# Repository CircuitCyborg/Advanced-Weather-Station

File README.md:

# Advanced-Weather-Station

Local Weather Station that incorporates weather from the user location and displays everything on a local desk base station.

Possible Future Features -

Incorporating forecast from a weather service onto the Base Station.
Communication between modules through the LAN
Limited Smart Home Automations through Base Station

To view the Weather Station in 3D Open this link: https://cad.onshape.com/documents/2aa1986e22143bf0c5bf430b/w/d39aab6bbb374c6101d395f4/e/43a2d6a15468c7d35dd3c23b?renderMode=0&uiState=6ae6a9e5bb2c688de4aefb5d

The purpose of designing this project was to have the most accurate weather information for my exact location. Weather apps are cool, but they are just a reading of where the weather module is for that company. My weather station gives a reading of what my exact location's weather is instead so I will have the most accurate weather data for my location.

For the few who want to build this themselves, there will be a bit of hand wiring that will have to happen. For this wiring, you will need 10 conductors for the direction sensor, 3 conductors for the temp/humidity sensor, 3 for the wind speed sensor, and 3 for the precipitation module. If you purchase enough, you should be able to use the extra ethercon cable for those conductors. When wiring, take your time, be patient with yourself, and have fun!

Wiring Diagram:

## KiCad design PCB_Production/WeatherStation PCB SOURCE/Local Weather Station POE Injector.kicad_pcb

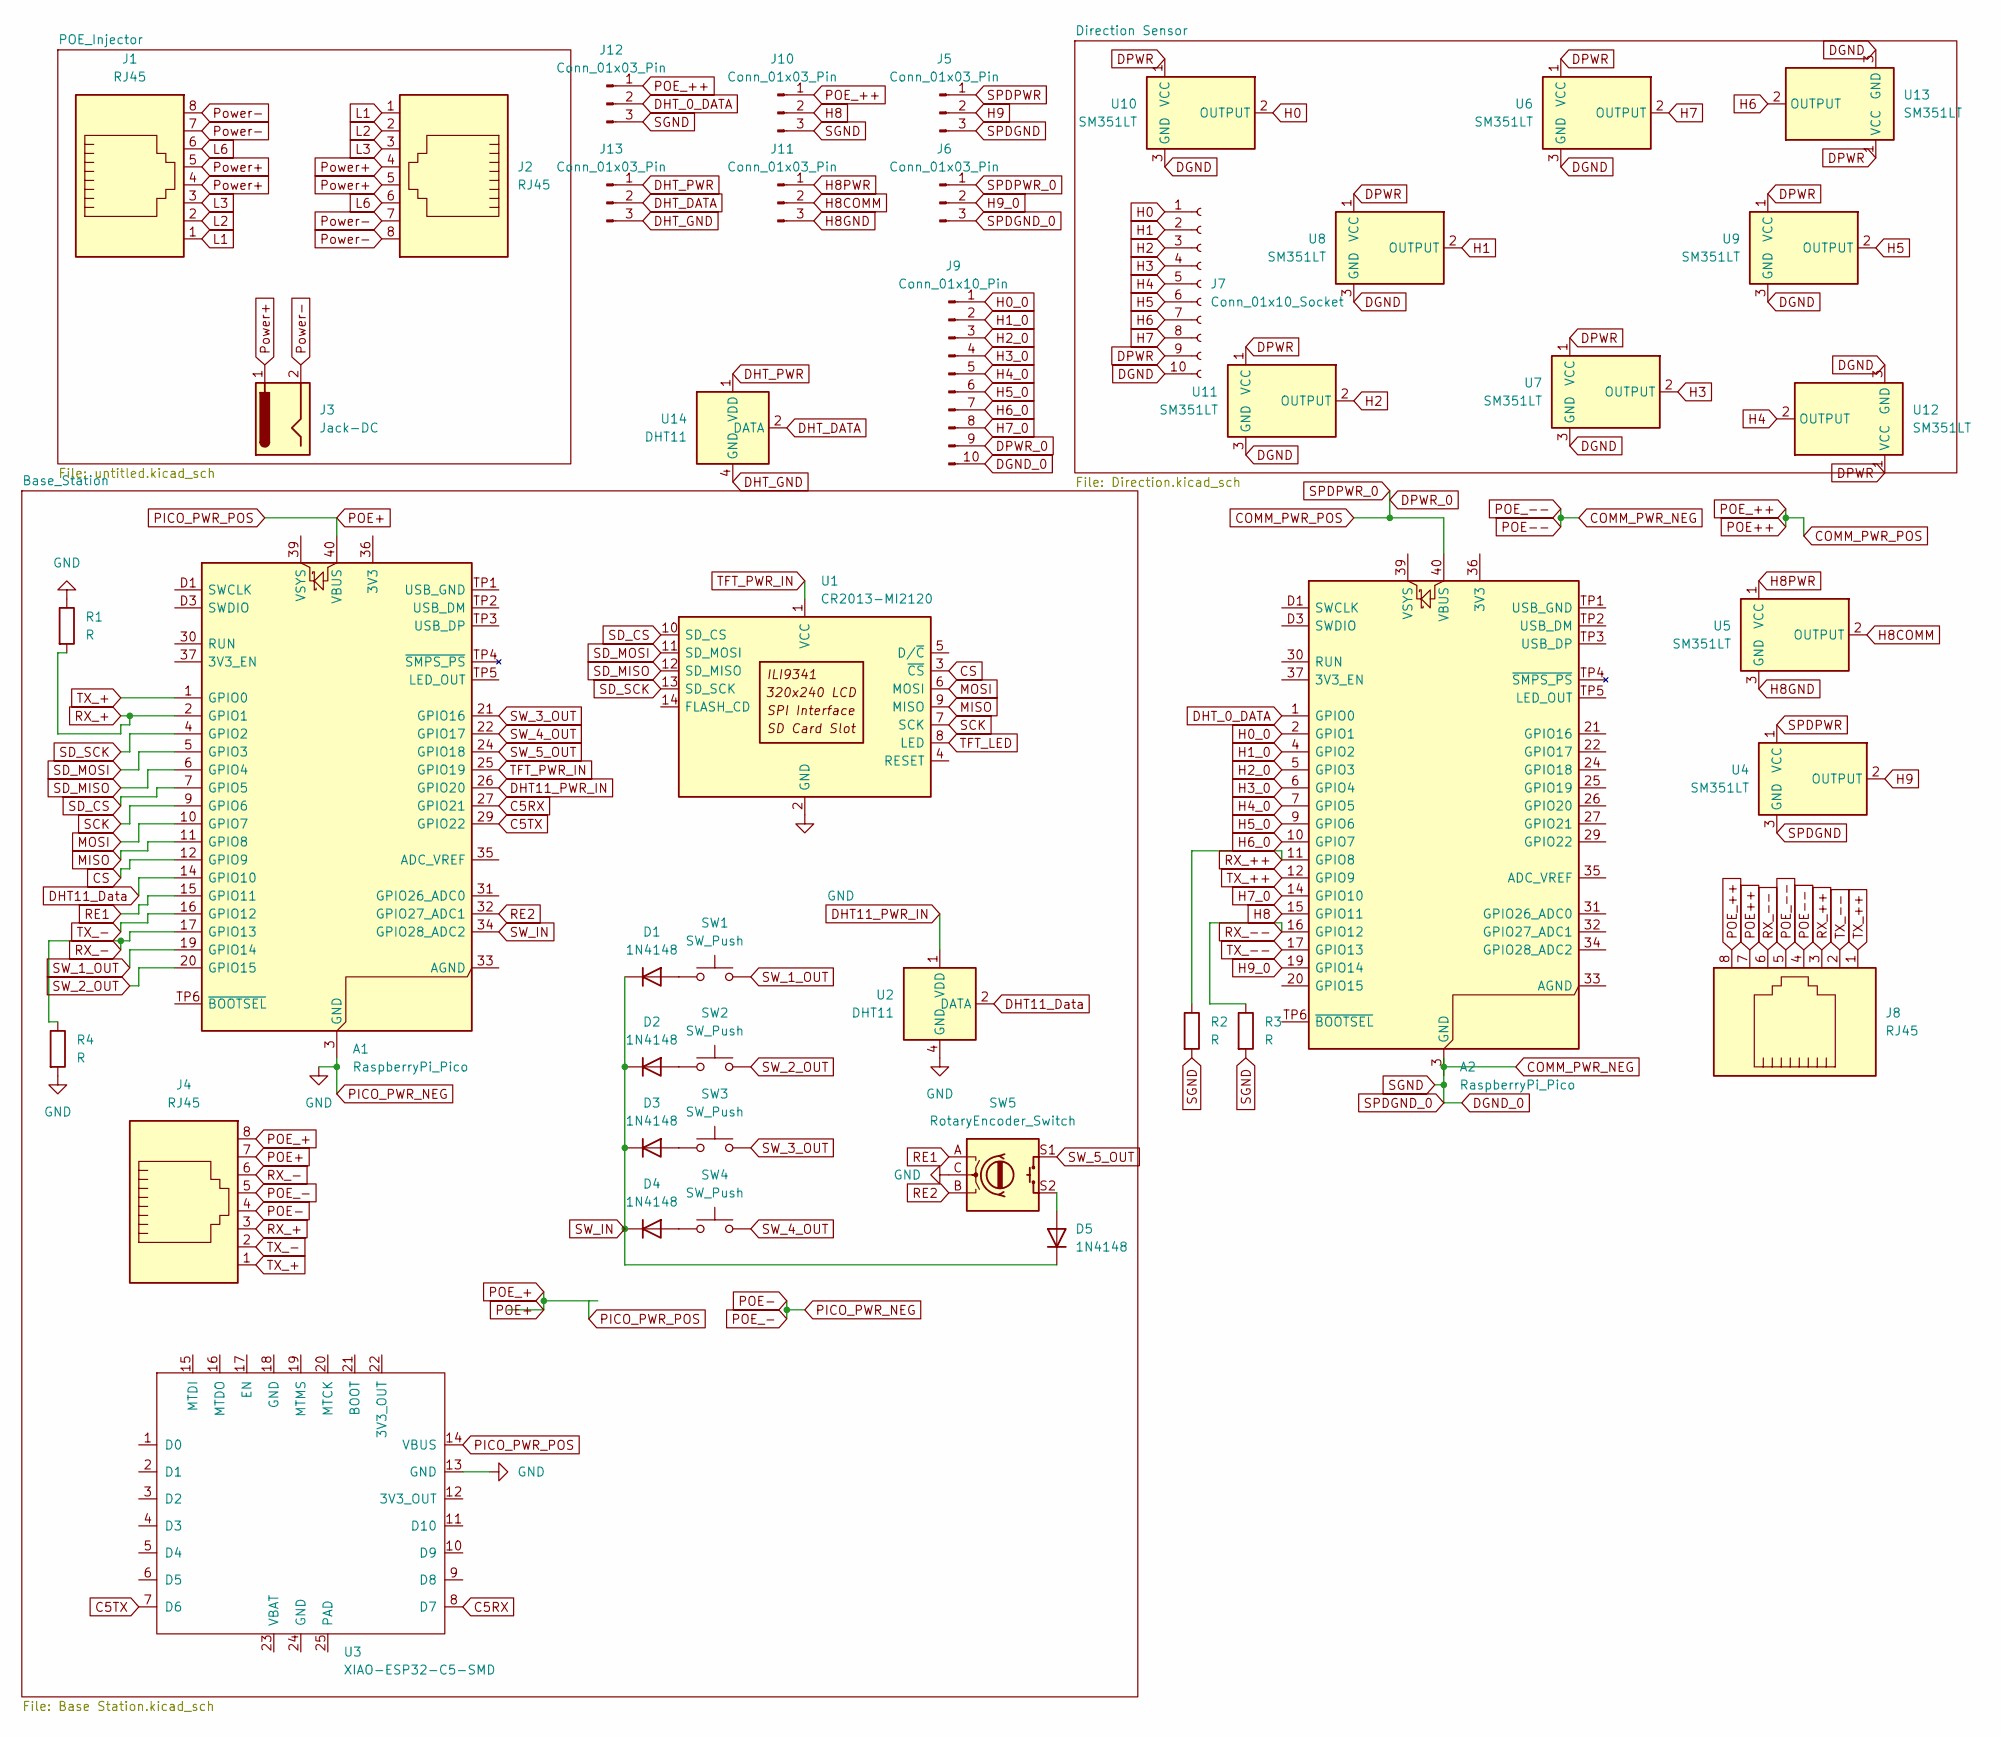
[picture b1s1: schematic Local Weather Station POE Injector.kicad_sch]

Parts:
A1, A2: RaspberryPi_Pico; RaspberryPi_Pico_Common_THT
D1, D2, D3, D4, D5: 1N4148; D_DO-35_SOD27_P7.62mm_Horizontal
J1, J2, J4, J8: RJ45; PinSocket_1x08_P2.54mm_Vertical
J3: Jack-DC; BarrelJack_CUI_PJ-063AH_Horizontal
J5, J6, J10, J11, J12, J13: Conn_01x03_Pin; PinSocket_1x03_P2.54mm_Vertical
J7: Conn_01x10_Socket; PinSocket_1x10_P2.54mm_Vertical
J9: Conn_01x10_Pin; PinSocket_1x10_P2.54mm_Vertical
R1, R2, R3, R4: R; R_Axial_DIN0207_L6.3mm_D2.5mm_P10.16mm_Horizontal
SW1, SW2, SW3, SW4: SW_Push; SW_PUSH_6mm
SW5: RotaryEncoder_Switch; RotaryEncoder_Alps_EC11E-Switch_Vertical_H20mm
U1: CR2013-MI2120
U2, U14: DHT11; Aosong_DHT11_5.5x12.0_P2.54mm
U3: XIAO-ESP32-C5-SMD; XIAO-RP2040-DIP
U4, U5, U6, U7, U8, U9, U10, U11, U12, U13: SM351LT; TO-92Flat

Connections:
C5RX: A1.27 (GPIO21), U3.8 (D7)
C5TX: A1.29 (GPIO22), U3.7 (D6)
COMM_PWR_NEG: J6.3, J8.4, J8.5, J9.10, J10.3, J12.3, R2.2, R3.2
COMM_PWR_POS: A2.40 (VBUS), J6.1, J8.7, J8.8, J9.9, J10.1, J12.1
CS: A1.12 (GPIO9), U1.3 (~CS)
DGND: J7.10, U6.3 (GND), U7.3 (GND), U8.3 (GND), U9.3 (GND), U10.3 (GND), U11.3 (GND), U12.3 (GND), U13.3 (GND)
DHT11_Data: A1.14 (GPIO10), U2.2 (DATA)
DHT11_PWR_IN: A1.26 (GPIO20), U2.1 (VDD)
DHT_0_DATA: A2.1 (GPIO0), J12.2
DHT_DATA: J13.2, U14.2 (DATA)
DHT_GND: J13.3, U14.4 (GND)
DHT_PWR: J13.1, U14.1 (VDD)
DPWR: J7.9, U6.1 (VCC), U7.1 (VCC), U8.1 (VCC), U9.1 (VCC), U10.1 (VCC), U11.1 (VCC), U12.1 (VCC), U13.1 (VCC)
H0: J7.1, U10.2 (OUTPUT)
H0_0: A2.2 (GPIO1), J9.1
H1: J7.2, U8.2 (OUTPUT)
H1_0: A2.4 (GPIO2), J9.2
H2: J7.3, U11.2 (OUTPUT)
H2_0: A2.5 (GPIO3), J9.3
H3: J7.4, U7.2 (OUTPUT)
H3_0: A2.6 (GPIO4), J9.4
H4: J7.5, U12.2 (OUTPUT)
H4_0: A2.7 (GPIO5), J9.5
H5: J7.6, U9.2 (OUTPUT)
H5_0: A2.9 (GPIO6), J9.6
H6: J7.7, U13.2 (OUTPUT)
H6_0: A2.10 (GPIO7), J9.7
H7: J7.8, U6.2 (OUTPUT)
H7_0: A2.14 (GPIO10), J9.8
H8: A2.15 (GPIO11), J10.2
H8COMM: J11.2, U5.2 (OUTPUT)
H8GND: J11.3, U5.3 (GND)
H8PWR: J11.1, U5.1 (VCC)
H9: J5.2, U4.2 (OUTPUT)
H9_0: A2.19 (GPIO14), J6.2
L1: J1.1, J2.1
L2: J1.2, J2.2
L3: J1.3, J2.3
L6: J1.6, J2.6
MISO: A1.11 (GPIO8), U1.9 (MISO)
MOSI: A1.10 (GPIO7), U1.6 (MOSI)
unnamed: A2.3 (GND), A2.8 (GND), A2.13 (GND), A2.18 (GND), A2.23 (GND), A2.28 (GND), A2.38 (GND), A2.D2 (GND)
unnamed: D1.2 (A), SW1.1
unnamed: D2.2 (A), SW2.1
unnamed: D3.2 (A), SW3.1
unnamed: D4.2 (A), SW4.1
unnamed: D5.2 (A), SW5.S2
PICO_PWR_NEG: A1.3 (GND), A1.8 (GND), A1.13 (GND), A1.18 (GND), A1.23 (GND), A1.28 (GND), A1.38 (GND), A1.D2 (GND), J4.4, J4.5, R1.1, R4.2, SW5.C, U1.2 (GND), U2.4 (GND), U3.13 (GND)
PICO_PWR_POS: A1.40 (VBUS), J4.7, J4.8, U3.14 (VBUS)
Power+: J1.4, J1.5, J2.4, J2.5, J3.1
Power-: J1.7, J1.8, J2.7, J2.8, J3.2
RE1: A1.15 (GPIO11), SW5.A
RE2: A1.32 (GPIO27_ADC1), SW5.B
RX_+: A1.2 (GPIO1), J4.3, R1.2
RX_++: A2.11 (GPIO8), J8.3, R2.1
RX_-: A1.17 (GPIO13), J4.6, R4.1
RX_--: A2.16 (GPIO12), J8.6, R3.1
SCK: A1.9 (GPIO6), U1.7 (SCK)
SD_CS: A1.7 (GPIO5), U1.10 (SD_CS)
SD_MISO: A1.6 (GPIO4), U1.12 (SD_MISO)
SD_MOSI: A1.5 (GPIO3), U1.11 (SD_MOSI)
SD_SCK: A1.4 (GPIO2), U1.13 (SD_SCK)
SPDGND: J5.3, U4.3 (GND)
SPDPWR: J5.1, U4.1 (VCC)
SW_1_OUT: A1.19 (GPIO14), SW1.2
SW_2_OUT: A1.20 (GPIO15), SW2.2
SW_3_OUT: A1.21 (GPIO16), SW3.2
SW_4_OUT: A1.22 (GPIO17), SW4.2
SW_5_OUT: A1.24 (GPIO18), SW5.S1
SW_IN: A1.34 (GPIO28_ADC2), D1.1 (K), D2.1 (K), D3.1 (K), D4.1 (K), D5.1 (K)
TFT_LED: U1.8 (LED)
TFT_PWR_IN: A1.25 (GPIO19), U1.1 (VCC)
TX_+: A1.1 (GPIO0), J4.1
TX_++: A2.12 (GPIO9), J8.1
TX_-: A1.16 (GPIO12), J4.2
TX_--: A2.17 (GPIO13), J8.2

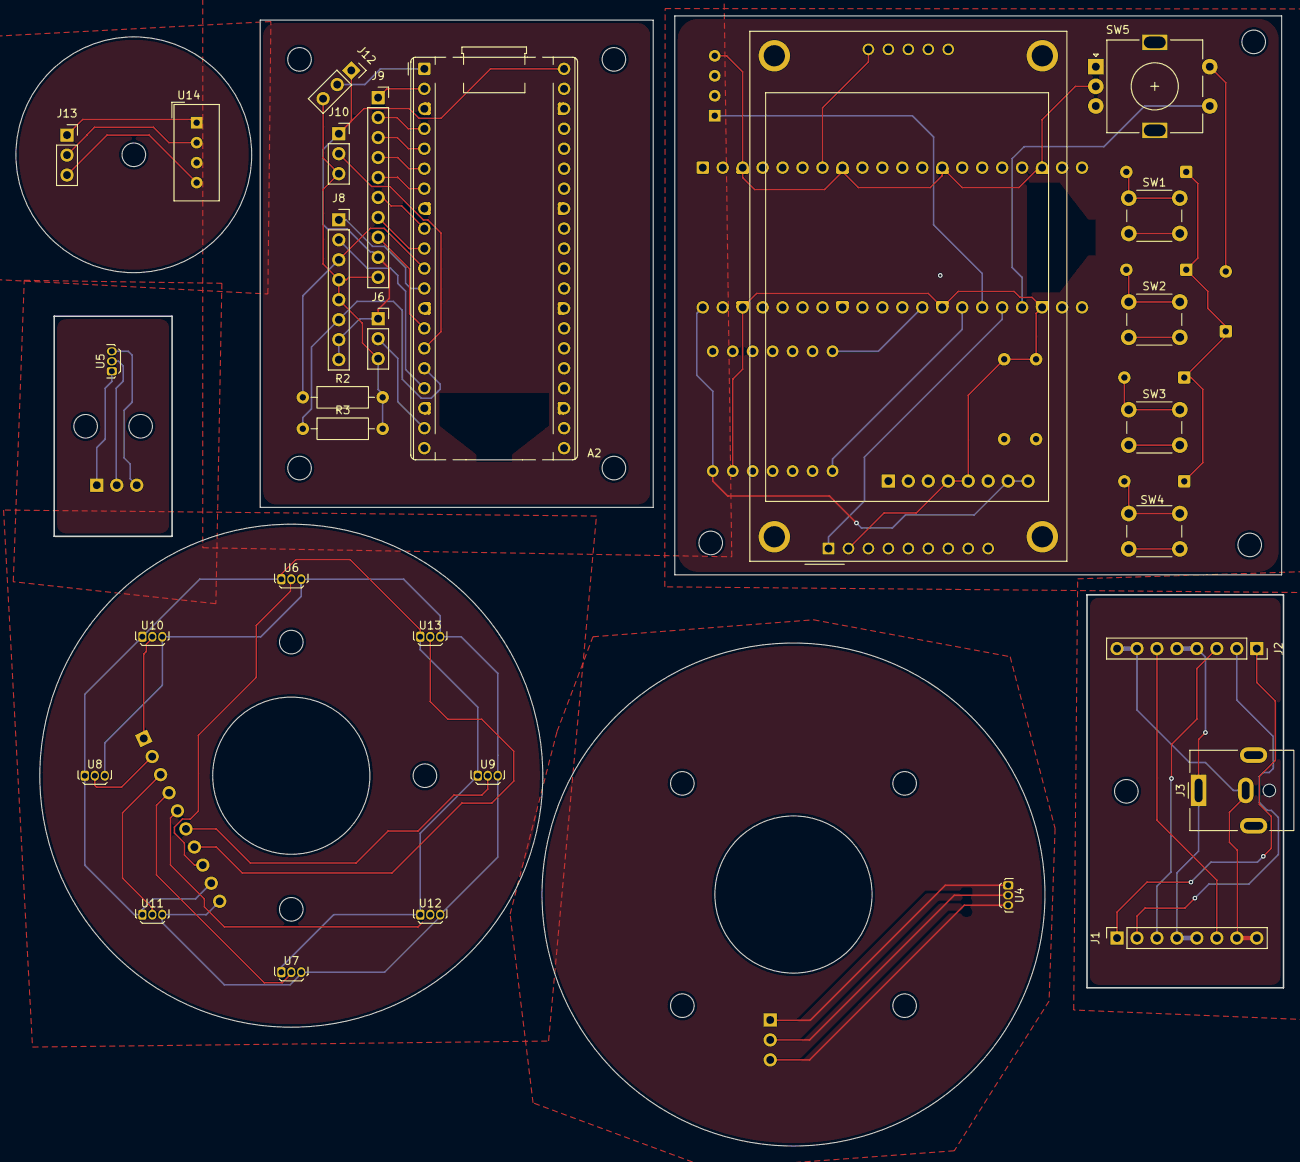
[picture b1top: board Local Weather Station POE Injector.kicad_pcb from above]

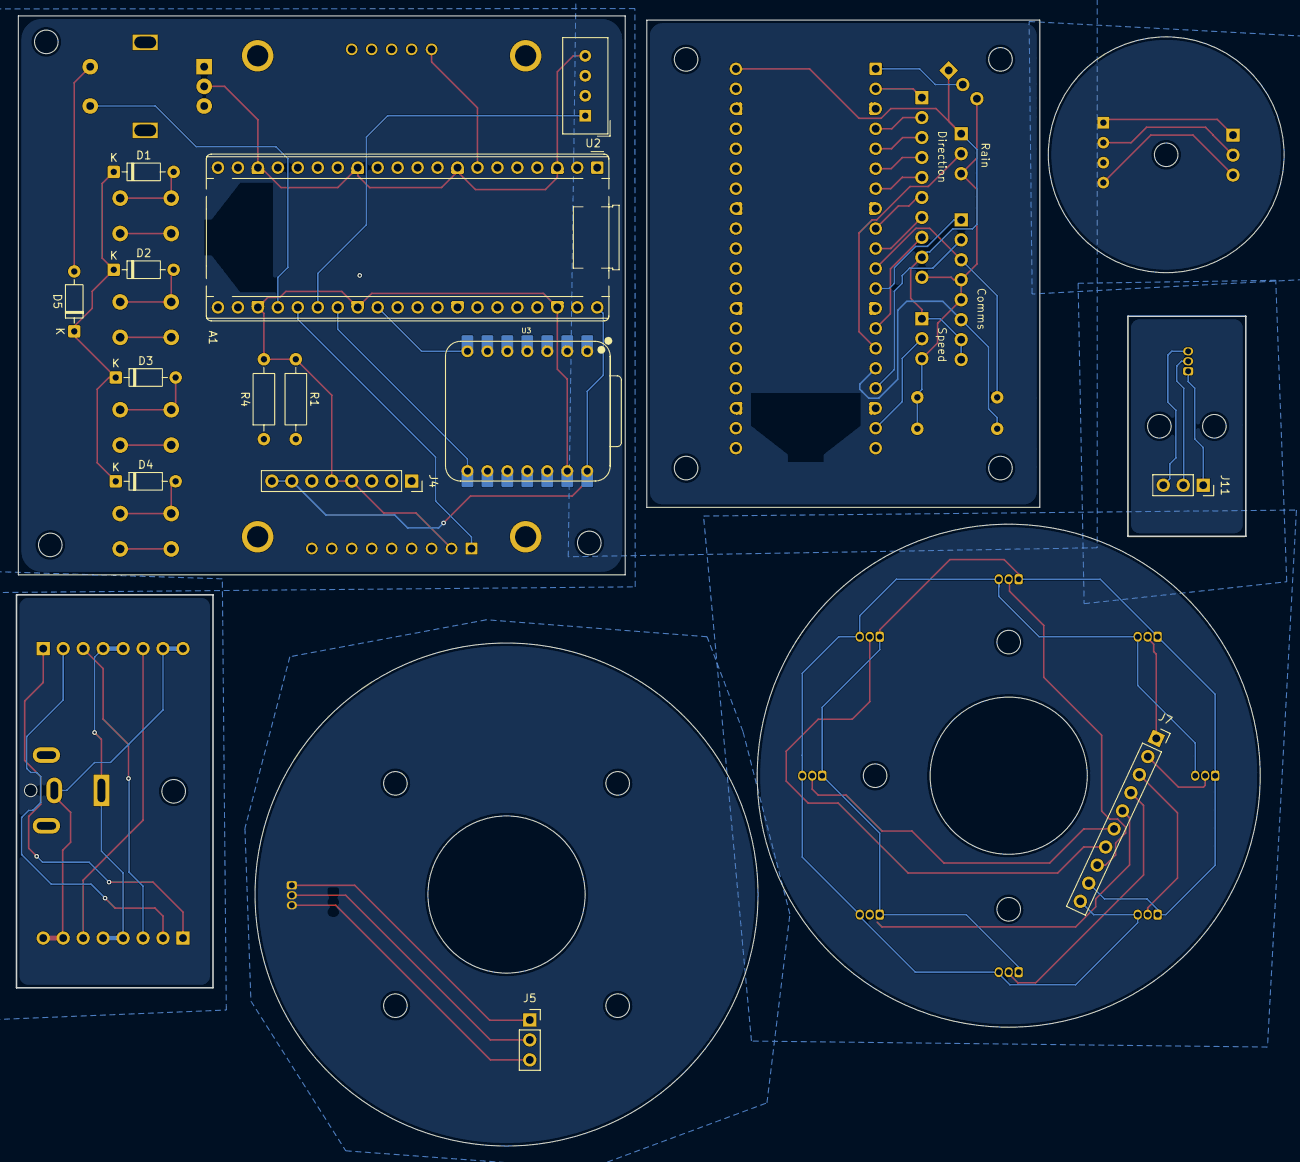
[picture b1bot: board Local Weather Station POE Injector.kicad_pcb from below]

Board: 6 copper layers, 161.3 x 143.8 mm, 43 parts (14 on the bottom side), 75 nets.
